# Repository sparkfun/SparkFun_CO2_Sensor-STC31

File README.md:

[*SparkFun CO<sub>2</sub> Sensor - STC31 (Qwiic) (SEN-29260)*](https://www.sparkfun.com/sparkfun-co2-sensor-stc31-qwiic.html)

The SparkFun CO<sub>2</sub> Sensor - STC31 is a Qwiic breakout featuring the STC31 CO<sub>2</sub> and SHTC3 Temperature and Humidity sensors from Sensirion<sup>&reg;</sup> to accurately measure CO<sub>2</sub> concentrations up to 100% with high repeatability and long-term stability with humidity and temperature compensation via the built-in SHTC3. 

Repository Contents
-------------------

* **/docs** - GitHub Pages documentation files
* **/Documentation** - Datasheets, application notes, etc.
* **/Hardware** - Eagle design files (.brd, .sch)
* **/Production** - Production panel files (.brd)

Documentation
--------------
* **[STC3x Arduino Library](https://github.com/sparkfun/SparkFun_STC3x_Arduino_Library)** - Arduino library for the SparkFun CO<sub>2</sub> Sensor - STC31 (Qwiic).
* **[STC3x Python Package](https://github.com/sparkfun/qwiic_stc3x_py) - Python package for the SparkFun CO<sub>2</sub> Sensor - STC31 (Qwiic).
* **[Hookup Guide](https://docs.sparkfun.com/SparkFun_CO2_Sensor-STC31)** - Basic hookup guide for the SparkFun CO<sub>2</sub> Sensor - STC31 (Qwiic.

Product Versions
----------------
* [SEN-29260](https://www.sparkfun.com/sparkfun-co2-sensor-stc31-qwiic.html) - SparkFun "Reds" release of the CO<sub>2</sub> Sensor - STC31 (Qwiic).
* [SPX-18385](https://www.sparkfun.com/co-sensor-stc31-qwiic.html) - Initial SparkX release of the CO<sub>2</sub> Sensor - STC31 (Qwiic)

License Information
-------------------

This product is _**open source**_! 

Please review the LICENSE.md file for license information. 

If you have any questions or concerns on licensing, please contact technical support on our [SparkFun forums](https://forum.sparkfun.com/viewforum.php?f=152).

Distributed as-is; no warranty is given.

- Your friends at SparkFun.

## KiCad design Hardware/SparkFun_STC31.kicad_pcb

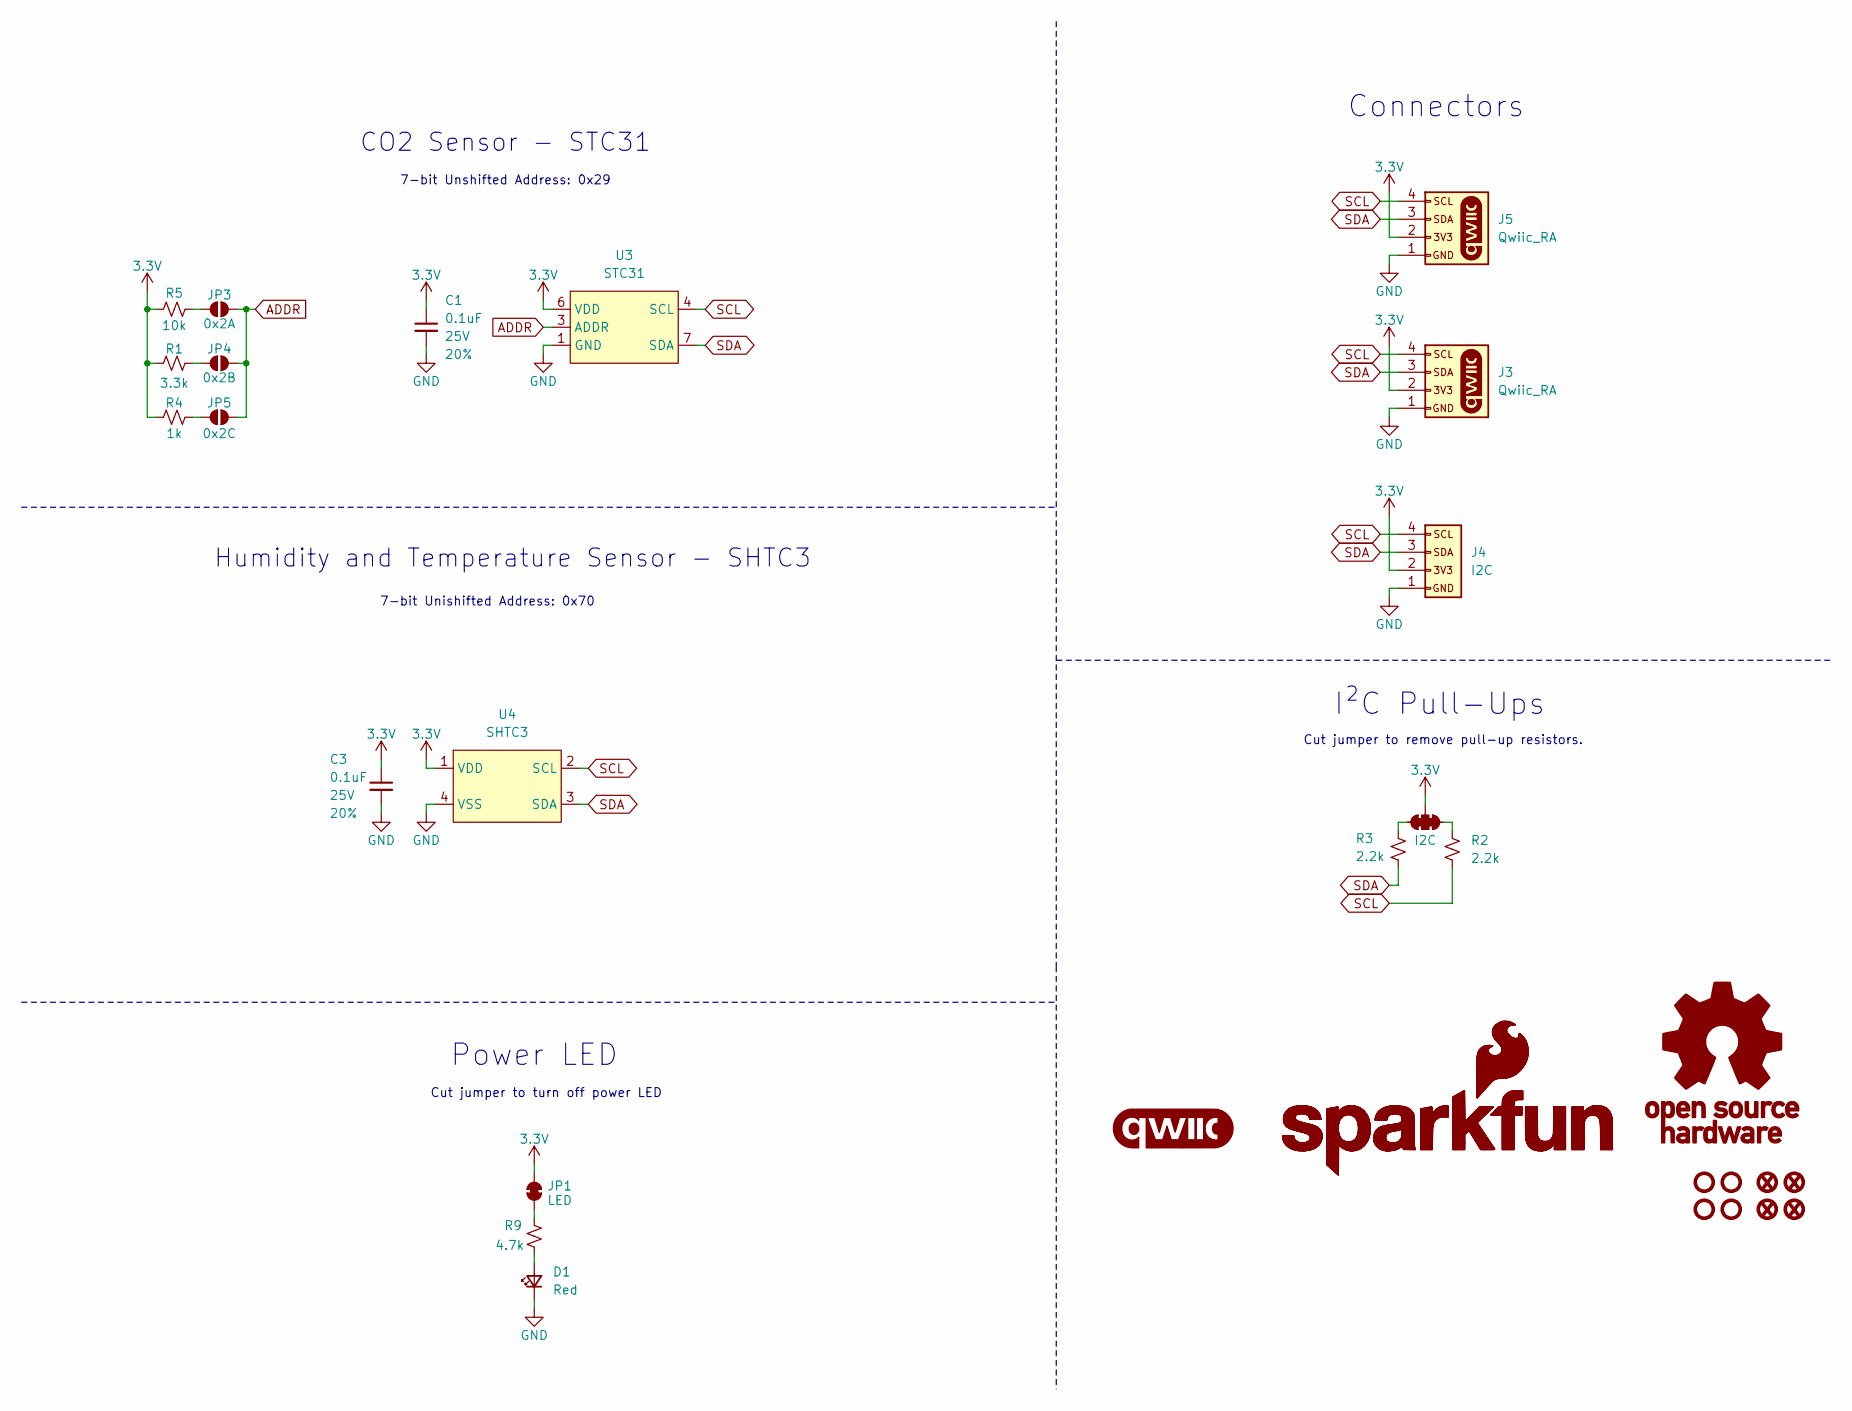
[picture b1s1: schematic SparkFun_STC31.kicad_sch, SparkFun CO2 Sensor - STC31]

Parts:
C1, C3: 0.1uF; C_0603_1608Metric; Voltage 25V; Tolerance 20%
D1: Red; LED_0603_1608Metric_Red
FID1, FID2, FID3, FID4: Fiducial_0.5mm; Fiducial_0.5mm_Mask1mm
G1: qwiic_Logo
G2: SparkFun_Logo; SparkFun_Logo_8mm
G3: SparkFun_Logo
G4: OSHW_Logo; Creative_Commons_License
J3, J5: Qwiic_RA; JST_SMD_1.0mm-4_Black
J4: I2C; 1x04
JP1: LED; Jumper_2_NC_Trace
JP2: I2C; Jumper_3_NC-2_Trace
JP3: 0x2A; Jumper_2_NO
JP4: 0x2B; Jumper_2_NO
JP5: 0x2C; Jumper_2_NO
R1: 3.3k; R_0603_1608Metric
R2, R3: 2.2k; R_0603_1608Metric
R4: 1k; R_0603_1608Metric
R5: 10k; R_0603_1608Metric
R9: 4.7k; R_0603_1608Metric
ST1, ST2, ST3, ST4: Standoff
U3: STC31
U4: SHTC3

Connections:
3.3V: C1.1, C3.1, J3.2, J4.2, J5.2, JP1.2 (B), JP2.2 (B), R1.1, R4.1, R5.1, U3.6 (VDD), U4.1 (VDD)
ADDR: JP3.2 (B), JP4.2 (B), JP5.2 (B), U3.3 (ADDR)
GND: C1.2, C3.2, D1.1 (K), J3.1, J4.1, J5.1, U3.1 (GND), U3.5 (GND), U3.9 (GND), U3.11 (GND), U4.4 (VSS)
unnamed: D1.2 (A), R9.2
unnamed: JP1.1 (A), R9.1
unnamed: JP2.1 (A), R2.2
unnamed: JP2.3 (C), R3.2
unnamed: JP3.1 (A), R5.2
unnamed: JP4.1 (A), R1.2
unnamed: JP5.1 (A), R4.2
SCL: J3.4, J4.4, J5.4, R2.1, U3.4 (SCL), U4.2 (SCL)
SDA: J3.3, J4.3, J5.3, R3.1, U3.7 (SDA), U4.3 (SDA)

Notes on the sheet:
7-bit Unishifted Address: 0x70
CO2 Sensor - STC31
7-bit Unshifted Address: 0x29
Humidity and Temperature Sensor - SHTC3
I²C Pull-Ups
Cut jumper to turn off power LED
Cut jumper to remove pull-up resistors.
Power LED
Connectors

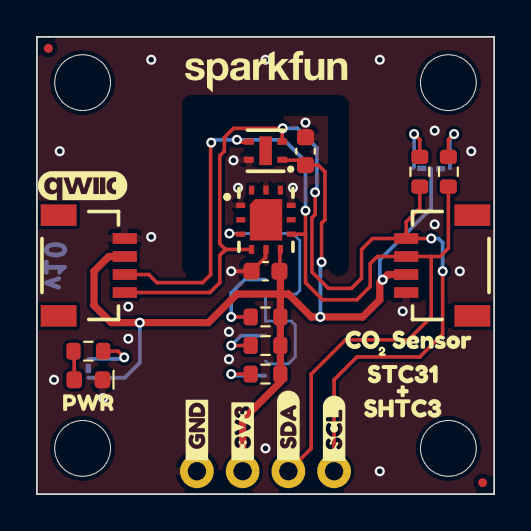
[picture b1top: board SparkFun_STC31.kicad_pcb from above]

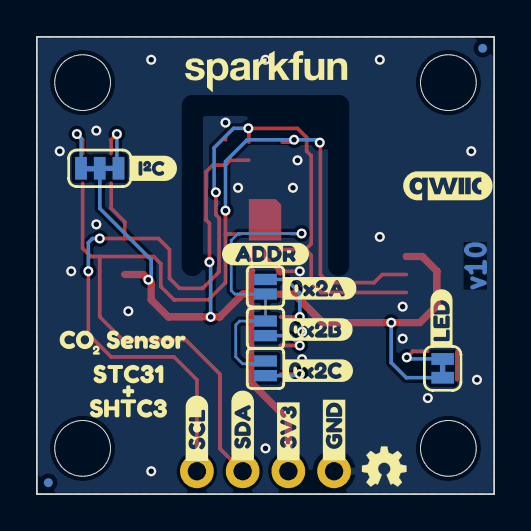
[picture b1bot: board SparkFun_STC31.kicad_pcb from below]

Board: 2 copper layers, 25.4 x 25.4 mm, 54 parts (23 on the bottom side), 12 nets.

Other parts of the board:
Ref**: Val**; OSHW_Logo_2.5mm
kibuzzard-65A8A8B4: G***; kibuzzard-65A8A8B4
kibuzzard-67BF7C99: G***; kibuzzard-67BF7C99
kibuzzard-67BF7CFE: G***; kibuzzard-67BF7CFE
kibuzzard-67BF7D12: G***; kibuzzard-67BF7D12
kibuzzard-67BF7EBF: G***; kibuzzard-67BF7EBF
kibuzzard-67BF7F2F: G***; kibuzzard-67BF7F2F
kibuzzard-67BF7F13: G***; kibuzzard-67BF7F13
kibuzzard-67D9D97F: G***; kibuzzard-67D9D97F
kibuzzard-67D9E7C1: G***; kibuzzard-67D9E7C1
kibuzzard-682CCCFC, kibuzzard-682CCCFC#2: G***; kibuzzard-682CCCFC
kibuzzard-682CCD34, kibuzzard-682CCD34#2: G***; kibuzzard-682CCD34
kibuzzard-6813D00F, kibuzzard-6813D00F#2: G***; kibuzzard-6813D00F
kibuzzard-6813D1B2: G***; kibuzzard-6813D1B2
kibuzzard-6813D10D: G***; kibuzzard-6813D10D
kibuzzard-6813D11F: G***; kibuzzard-6813D11F
kibuzzard-6813D116: G***; kibuzzard-6813D116
kibuzzard-68489B7D, kibuzzard-68489B7D#2: G***; kibuzzard-68489B7D
kibuzzard-68489B76, kibuzzard-68489B76#2: G***; kibuzzard-68489B76
kibuzzard-681398D9: G***; kibuzzard-681398D9
kibuzzard-681398E8: G***; kibuzzard-681398E8

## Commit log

2025-05-01 Removes unnecessary files, adds outline for design
2025-05-01 Updates the gitignore, finishes the schematic
2025-05-01 Cleans out the PCB
2025-05-01 Places parts within the board's outline
2025-05-01 Attempts to add some milling
2025-05-01 Stacks ground pins for STC31
2025-05-01 Slightly adjusts schematic
2025-05-01 Adds route out
2025-05-01 Routes most air-wires
2025-05-01 Routes a few more air-wires
2025-05-01 Slightly adjusts some objects
2025-05-01 Finishes routing the board, adds silk
2025-05-06 Moves things ever so slightly
2025-05-20 Adds 2.2k resistors, changes direction of SCL flag
2025-05-20 Fix silk
2025-05-21 Replaces STC31 and SHTC3 with updated symbols/footprints
2025-05-21 Moves some stuff around
2025-06-10 Moves Production files to the correct folder
2025-06-10 Adds silk for SHTC3 part number to silk
2025-06-10 Repanelizes the product that now has silk reflecting the other part on it
2025-07-22 Cams the panel again but adds Kicad Milling layer to CAM output so that it correctly puts it onto "knockout"
2025-08-18 Docs update from template
    Updating documentation files from template.
2025-08-21 Docs review & photos
    Final review updates. Added photos, board and component files & GH pages build files.
2025-08-21 Deployed 7dca026 with MkDocs version: 1.6.1

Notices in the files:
parts and their libraries:
https://creativecommons.org/licenses/by-sa/4.0
Released under the Creative Commons Attribution Share-Alike 4.0 License
